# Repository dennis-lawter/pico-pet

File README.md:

# Pico Pet
A virtual pet that requires the user to complete pomodoros for the health of their pet.

## Hardware
- Raspberry Pi Pico
    - [Raspberry Pi Pico](https://www.raspberrypi.com/products/raspberry-pi-pico/) for development
    - [Waveshare RP2040-Tiny](https://www.waveshare.com/rp2040-tiny.htm) for release
- [Waveshare 1.44" LCD](https://www.waveshare.com/pico-lcd-1.44.htm)
- [DS3231](https://www.amazon.com/dp/B09KPC8JZQ/)
- Any 5v to 3v3 shifter for the DS3231, [for example](https://www.amazon.com/dp/B07LG646VS/)
- Any 5v speaker or buzzer, [for example](https://www.amazon.com/dp/B07P6X9YX7/)
- Any 3v-5v vibrating motor, [for example](https://www.amazon.com/dp/B073YFR5WR)

## NVM Utilization
The NVM (Non-Volatile Memory) module included with the DS3231 provides 4KiB arranged in 512 pages of 8 bytes each.

Permanent storage must be serializable to a specified number of pages, and write to an assigned page address.

Pages are addressed from hexidecimal 0x000 to 0x1ff.

| Page Start | Page End | Module |
| --- | --- | --- |
| 000 | 000 | Header |
| 001 | 002 | Settings |
| 003 | 003 | Inventory |
| 004 | 005 | Pet |

*note: If the NVM becomes corrupted, try changing the const `NVM_SENTINEL` to force a header guard check failure. This will factory reset the device, and all data will be lost.*
|  | **Header** |
| --- | --- |
| 0 | if set to the `NVM_SENTINEL` value, then the EEPROM is assumed to contain a valid savefile |
| 1 |  |
| 2 |  |
| 3 |  |
| 4 |  |
| 5 |  |
| 6 |  |
| 7 |  |

|  | **Settings Page 1** | min | max |
| --- | --- | --- | --- |
| 0 | User brightness | 0 | 15 |
| 1 | User volume | 0 | 4 |
| 2 | *nyi* Vibration enabled | 0 | 1 |
| 3 | *nyi* 12hr clock enabled | 0 | 1 |
| 4 | *nyi* minutes before device sleeps | 1 | 90 |
| 5 |  |  |  |
| 6 |  |  |  |
| 7 |  |  |  |

|  | **Settings Page 2** | min | max |
| --- | --- | --- | --- |
| 0 | Pomodoro length in minutes | 1 | 90 |
| 1 | Short break length in minutes | 1 | 90 |
| 2 | Long break length in minutes | 1 | 90 |
| 3 | Cycles, aka number of pomodoros before a long rest | 1 | 9 |
| 4 | Pet feeding deadline hr | 0 | 23 |
| 5 | Pet feeding deadline min | 0 | 59 |
| 6 |  |  |  |
| 7 |  |  |  |

|  | **Inventory** | min | max |
| --- | --- | --- | --- |
| 0 | Tomatoes | 0 | 99 |
| 1 | Raspberries | 0 | 9 |
| 2 | Lower byte of juice value |  |  |
| 3 | Higher byte of juice value |  |  |
| 4 |  |  |  |
| 5 |  |  |  |
| 6 |  |  |  |
| 7 |  |  |  |

Max juice is 9999ml as a u16

|  | **Pet Page 1** |
| --- | --- |
| 0 | Birth Day |
| 1 | Birth Month |
| 2 | Birth Year |
| 3 |  |
| 4 |  |
| 5 |  |
| 6 |  |
| 7 |  |

|  | **Pet Page 2** |
| --- | --- |
| 0 | Current HP |
| 1 | Sickness |
| 2 | Daily Hunger |
| 3 | Last Fed Day |
| 4 | Last Fed Month |
| 5 | Last Fed Year |
| 6 |  |
| 7 |  |

Max HP = Daily Hunger + 4

Last Fed Year is probably excessive,
but it'd be a weird bug if someone started the pet up after exactly 1 year,
and their pet showed no signs of missed days of hunger...

## Pin Out For Raspberry Pico

```mermaid
graph LR
    subgraph RP2040
        Pin1
        Pin2
        %%Pin3[GND]
        Pin4
        Pin5
        Pin6
        Pin7
        %%Pin8[GND]
        Pin9
        %%Pin10
        Pin11
        Pin12
        %%Pin13[GND]
        Pin14
        Pin15
        Pin16
        Pin17
        %%Pin18[GND]
        %%Pin19
        Pin20
        %%Pin21
        Pin22
        %%Pin23[GND]
        %%Pin24
        %%Pin25
        %%Pin26
        %%Pin27
        %%Pin28[GND]
        %%Pin29
        %%Pin30
        %%Pin31
        %%Pin32
        %%Pin33[GND]
        %%Pin34
        %%Pin35
        %%Pin36[3V3_OUT]
        %%Pin37[3V3_EN]
        %%Pin38[GND]
        %%Pin39[VSYS]
        %%Pin40[VBUS]
    end

    subgraph RTC_NVM
        RTC_SDA
        RTC_SCL
        RTC_SQW
    end
    Pin1[Pin1 I2C0_SDA] --> RTC_SDA
    Pin2[Pin2 I2C0_SCL] --> RTC_SCL
    Pin7[Pin7 GP5] --> RTC_SQW

    subgraph BUZZER
        SPEAKER
    end
    Pin6[Pin6 PWM_A2] --> SPEAKER

    subgraph VIBRATION
        MOTOR
    end
    Pin9[Pin9 GP6] --> MOTOR

    subgraph LCD
        LCD_KEY2
        LCD_KEY3
        LCD_DC
        LCD_CS
        LCD_CLK
        LCD_DIN
        LCD_RST
        LCD_BL
        LCD_KEY0
        LCD_KEY1
    end
    Pin4[Pin4 GP2] --> LCD_KEY2
    Pin5[Pin5 GP3] --> LCD_KEY3
    Pin11[Pin11 GP8] --> LCD_DC
    Pin12[Pin12 SPI1_CSn] --> LCD_CS
    Pin14[Pin14 SPI1_SCK] --> LCD_CLK
    Pin15[Pin15 SPI1_TX] --> LCD_DIN
    Pin16[Pin16 SPI1_RX] --> LCD_RST
    Pin17[Pin17 PWM_B6] --> LCD_BL
    Pin20[Pin20 GP15] --> LCD_KEY0
    Pin22[Pin22 GP17] --> LCD_KEY1
```

## Pinout for Waveshare RP2040-Tiny
```mermaid
graph LR
    subgraph RP2040-Tiny
        TinyPin0
        TinyPin1
        TinyPin2
        TinyPin3
        TinyPin4
        TinyPin5
        TinyPin6
        %%TinyPin7
        TinyPin8
        TinyPin9
        TinyPin10
        TinyPin11
        TinyPin12
        TinyPin13
        %%TinyPin14
        TinyPin15
        %%TinyPin16
        %%TinyPin17
        %%TinyPin18
        TinyPin19
        %%TinyPin20
        %%TinyPin21[3V3]
        %%TinyPin22[GND]
        %%TinyPin23[5V]
    end

    subgraph RTC_NVM
        RTC_SDA
        RTC_SCL
        RTC_SQW
    end
    TinyPin0[TinyPin0 I2C0_SDA] --> RTC_SDA
    TinyPin1[TinyPin1 I2C0_SCL] --> RTC_SCL
    TinyPin5[TinyPin5 GP5] --> RTC_SQW

    subgraph BUZZER
        SPEAKER
    end
    TinyPin4[TinyPin4 PWM_A2] --> SPEAKER

    subgraph VIBRATION
        MOTOR
    end
    TinyPin6[TinyPin6 GP6] --> MOTOR

    subgraph LCD
        LCD_KEY2
        LCD_KEY3
        LCD_DC
        LCD_CS
        LCD_CLK
        LCD_DIN
        LCD_RST
        LCD_BL
        LCD_KEY0
        LCD_KEY1
    end
    TinyPin2[TinyPin2 GP2] --> LCD_KEY2
    TinyPin3[TinyPin3 GP3] --> LCD_KEY3
    TinyPin8[TinyPin8 GP8] --> LCD_DC
    TinyPin9[TinyPin9 SPI1_CSn] --> LCD_CS
    TinyPin10[TinyPin10 SPI1_SCK] --> LCD_CLK
    TinyPin11[TinyPin11 SPI1_TX] --> LCD_DIN
    TinyPin12[TinyPin12 SPI1_RX] --> LCD_RST
    TinyPin13[TinyPin13 PWM_B6] --> LCD_BL
    TinyPin15[TinyPin15 GP15] --> LCD_KEY0
    TinyPin19[TinyPin19 GP29] --> LCD_KEY1
```

## Development Breakboard Build
Below are my recommendations for how to build the development board.

### Shopping List
All amazon links are tracking free and affiliate free; feel free to source these where you wish, but compatability is not guaranteed for other similar products.
The current iteration of the software is absolutely tied to the LCD module below, as well as the combination DS3231 & AT24C32 board.
Theoretically any RTC and NVM module could replace the aformentioned, but the I2C addresses have been set to match the product below.
Additionally, any ST7735S driven 128x128 display could be adapted. All four buttons provided on the waveshare LCD hat are used as well.
- Components
    - Expansion Board https://www.amazon.com/dp/B08X6FPRYF/
    - Breakout Board https://www.amazon.com/dp/B0B982B9HV/
    - Breadboard https://www.amazon.com/dp/B07VFFXPH3/
    - LCD Module https://www.amazon.com/dp/B0957NJP97/
    - Raspberry Pico w/ presoldered headers https://www.amazon.com/dp/B08X7HN2VG/
    - RTC Board https://www.amazon.com/dp/B09KPC8JZQ/
    - Vibrating Motor https://www.amazon.com/dp/B073YFR5WR/
    - Piezo Buzzer https://www.amazon.com/dp/B07P6X9YX7/
- Tools/Resources
    - 22 AWG solid hookup wire https://www.amazon.com/dp/B07TX6BX47/
    - 22 AWG wire stripper https://www.amazon.com/dp/B06X9875Z7/
    - CR2032 battery https://www.amazon.com/dp/B071D4DKTZ/
    - Command strip https://www.amazon.com/dp/B07P32RHQ4/

### Assembly
1. Socket the Raspberry Pico into center of the Expansion Board.
2. Socket the LCD Module into the left slot of the Expansion Board.
3. Using a command strip, attach the breadboard to the flat side of the breakout board.
    - The 1A point of the breadboard should be in the top left, near where the word VBUS is printed on the back of the breakout board.
    - While many breadboards do come with stickers, there is often no solid insulating layer for the conductive rails, and the breakout board has sharp solder points that can stab through this thin soft layer. Whatever you do, I recommend insulating these two boards or you will risk a short...
4. Connect the breakout terminal VSYS and tie point 1A on the breadboard, preferably using a red wire.
    - I recommend running this wire over the top of the board rather than the side as it would be natural to do, because there will be essentially no space between the Raspberry Pico and this specific Breakout Board when they are eventually mated.
5. Connect the breakout terminal GND (the one adjacent to VSYS) and tie point 2A on the breadboard, preferably using a black wire.
    - Again, I recommend running this wire over the top of the board.
6. Connect the data lines to the breadboard, this time allowing the wires to wrap around the side of the board (recommended colors in parenthesis):
    - GP0 to J1 (green)
    - GP1 to J2 (white)
    - GP4 to J5 (yellow)
    - GP5 to J6 (blue)
    - GP6 to J7 (green)
7. Connect new lines on the breadboard for the RTC module:
    - C2 to C3 (black)
    - D1 to D4 (red)
    - H1 to B5 (green)
    - H2 to B6 (white)
    - H6 to B7 (blue) (I recommend routing this cable up then following the other 2 data lines)
8. Connect new lines on the breadboard for the piezo buzzer:
    - G5 to F17 (orange)
    - E2 to G13 (black) (I recommend routing this along the top side, then down the gap I left in the I column)
9. Connect new lines on the breadboard for the vibration motor:
    - G7 to K16 (green)
    - F13 to F15 (black)
10. Stick the vibration motor onto the bottom of the breadboard.
11. Attach the vibration motor wires (letting the wires lay to the right):
    - red wire to G16
    - blue wire to G15
12. Place the piezo buzzer onto pins J17 and J13 (placement will secure the vibration motor wires)
13. Insert a CR2032 battery into the RTC module.
14. Place the RTC module onto pins A3, A4, A5, A6, A7, and A8.
15. Finally, socket the breakout board onto the right slot of the Expansion Board.

### Development Environment Setup
#### NixOS
I recommend running the following to open the VSCodium development environment:
```bash
nix develop --command codium .
```

You can of course just use whatever text editor you like, and simply enter the flake in a terminal with:
```bash
nix develop
```

#### Arch
```
sudo pacman -S rustup
rustup default nightly
cargo install elf2uf2-rs
```
When the pico is plugged in you'll be prompted to mount the device. You must mount and run the device for this process to complete successfully.

#### Other Linux Distros
You'll need Rust installed and set to nightly-2023-11-16. Other versions may not be supported. You will likely also need udev to detect the raspberry pico. To use the makefile, you'll also want gnu make. You can review the `flake.nix` and attempt to reproduce it in your own OS.

### First Time Setup
Your first time opening this repo, you'll need to setup the dependencies and enable the thumbv6m-none-eabi target. This has been automated for you:
```bash
make init
```

### Running The Code
The build process performs a number of actions. The sprites will be converted from PNG files to raw binary files containing RGB332 data. Fonts will be converted from PNG files to binary files containg black&white data. The custom PEAT audio files will be converted from plaintext files to the binary custom BEAT format. With all assets converted, the project will finally build and attempt to upload.

All of this is as simple as invoking:
```bash
make run
```

## Attributions
Placeholder artwork (lofi.png) copyright belongs to Juan Pablo Machado.

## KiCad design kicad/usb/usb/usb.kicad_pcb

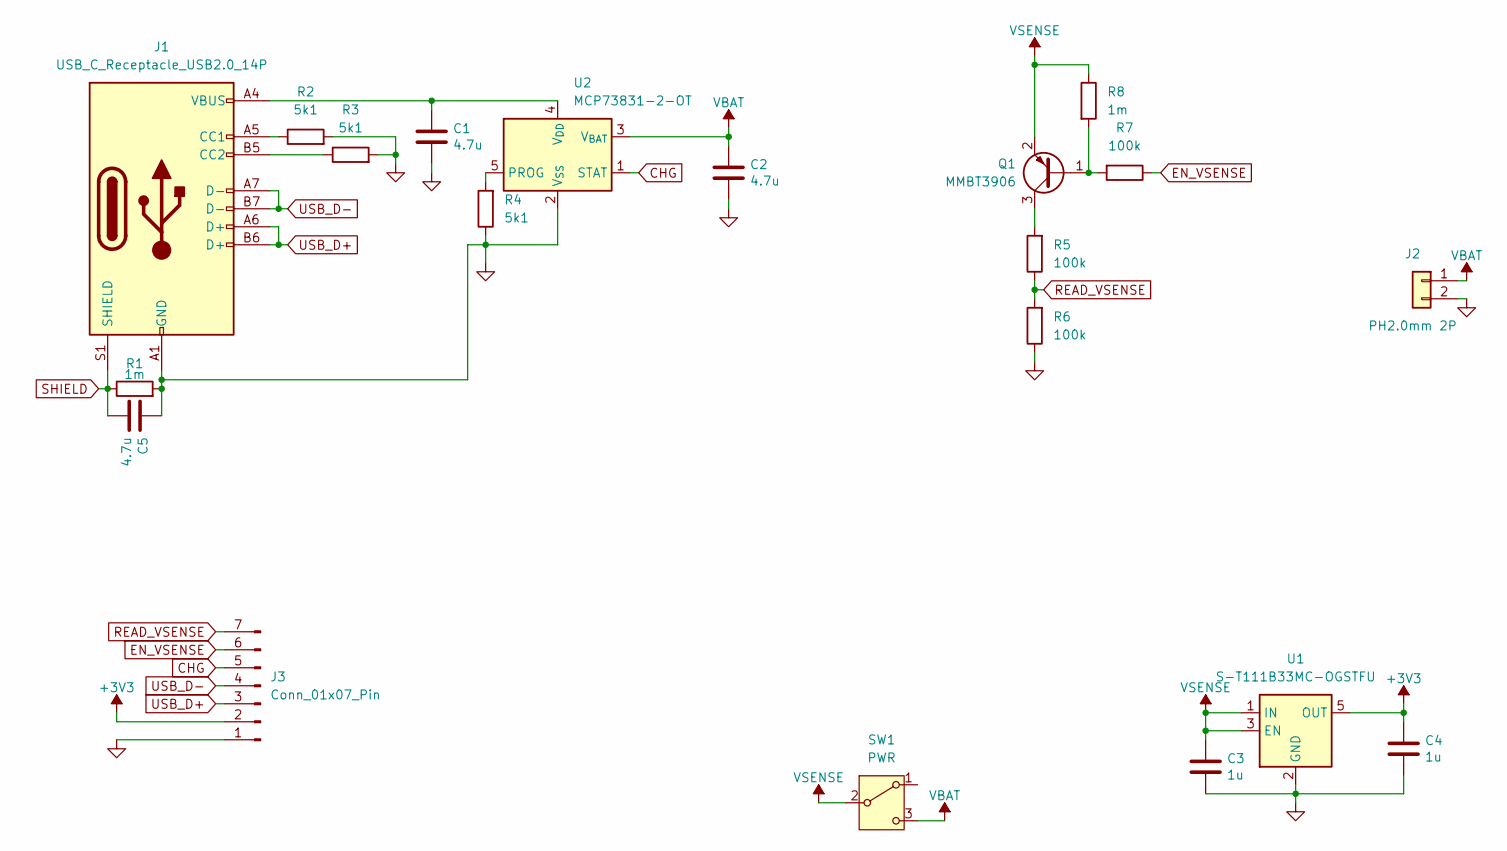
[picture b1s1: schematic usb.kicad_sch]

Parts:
C1, C2: 4.7u; C_0805_2012Metric; LCSC C15850
C3, C4: 1u; C_0805_2012Metric; LCSC C15850
C5: 4.7u; C_0603_1608Metric_Pad1.08x0.95mm_HandSolder; LCSC C15850
J1: USB_C_Receptacle_USB2.0_14P; USB_C_Receptacle_GCT_USB4105-xx-A_16P_TopMnt_Horizontal
J2: PH2.0mm 2P; JST_PH_S2B-PH-K_1x02_P2.00mm_Horizontal; LCSC C124375
J3: Conn_01x07_Pin; PinHeader_1x07_P2.54mm_Vertical
Q1: MMBT3906; SOT-23
R1: 1m; R_0603_1608Metric_Pad0.98x0.95mm_HandSolder
R2, R3, R4: 5k1; R_0201_0603Metric_Pad0.64x0.40mm_HandSolder
R5, R6, R7: 100k; R_0402_1005Metric_Pad0.72x0.64mm_HandSolder
R8: 1m; R_0402_1005Metric_Pad0.72x0.64mm_HandSolder
SW1: PWR; SW_Slide_SPDT_Angled_CK_OS102011MA1Q
U1: S-T111B33MC-OGSTFU; SOT-23-5
U2: MCP73831-2-OT; SOT-23-5

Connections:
+3V3: C4.1, J3.2, U1.5 (OUT)
CHG: J3.5, U2.1 (STAT)
EN_VSENSE: J3.6, R7.1
GND: C1.2, C2.2, C3.2, C4.2, C5.1, J1.A1 (GND), J1.A12 (GND), J1.B1 (GND), J1.B12 (GND), J2.2, J3.1, R1.2, R2.2, R3.2, R4.1, R6.1, U1.2 (GND), U1.4 (GND), U2.2 (V_{SS})
unnamed: J1.A5 (CC1), R2.1
unnamed: J1.B5 (CC2), R3.1
unnamed: Q1.1 (B), R7.2, R8.2
unnamed: Q1.3 (C), R5.2
unnamed: R4.2, U2.5 (PROG)
unnamed: C1.1, J1.A4 (VBUS), J1.A9 (VBUS), J1.B4 (VBUS), J1.B9 (VBUS), U2.4 (V_{DD})
READ_VSENSE: J3.7, R5.1, R6.2
SHIELD: C5.2, J1.S1 (SHIELD), R1.1
USB_D+: J1.A6 (D+), J1.B6 (D+), J3.3
USB_D-: J1.A7 (D-), J1.B7 (D-), J3.4
VBAT: C2.1, J2.1, SW1.3 (C), U2.3 (V_{BAT})
VSENSE: C3.1, Q1.2 (E), R8.1, SW1.2 (B), U1.1 (IN), U1.3 (EN)

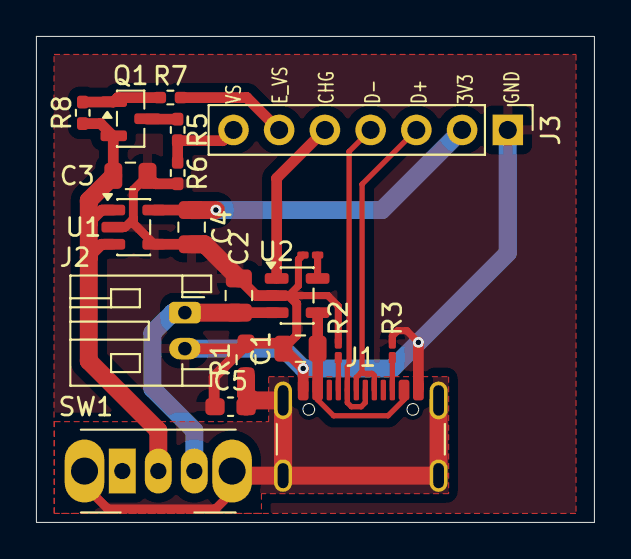
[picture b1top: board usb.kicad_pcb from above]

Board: 2 copper layers, 31.0 x 27.0 mm, 20 parts (0 on the bottom side), 16 nets.

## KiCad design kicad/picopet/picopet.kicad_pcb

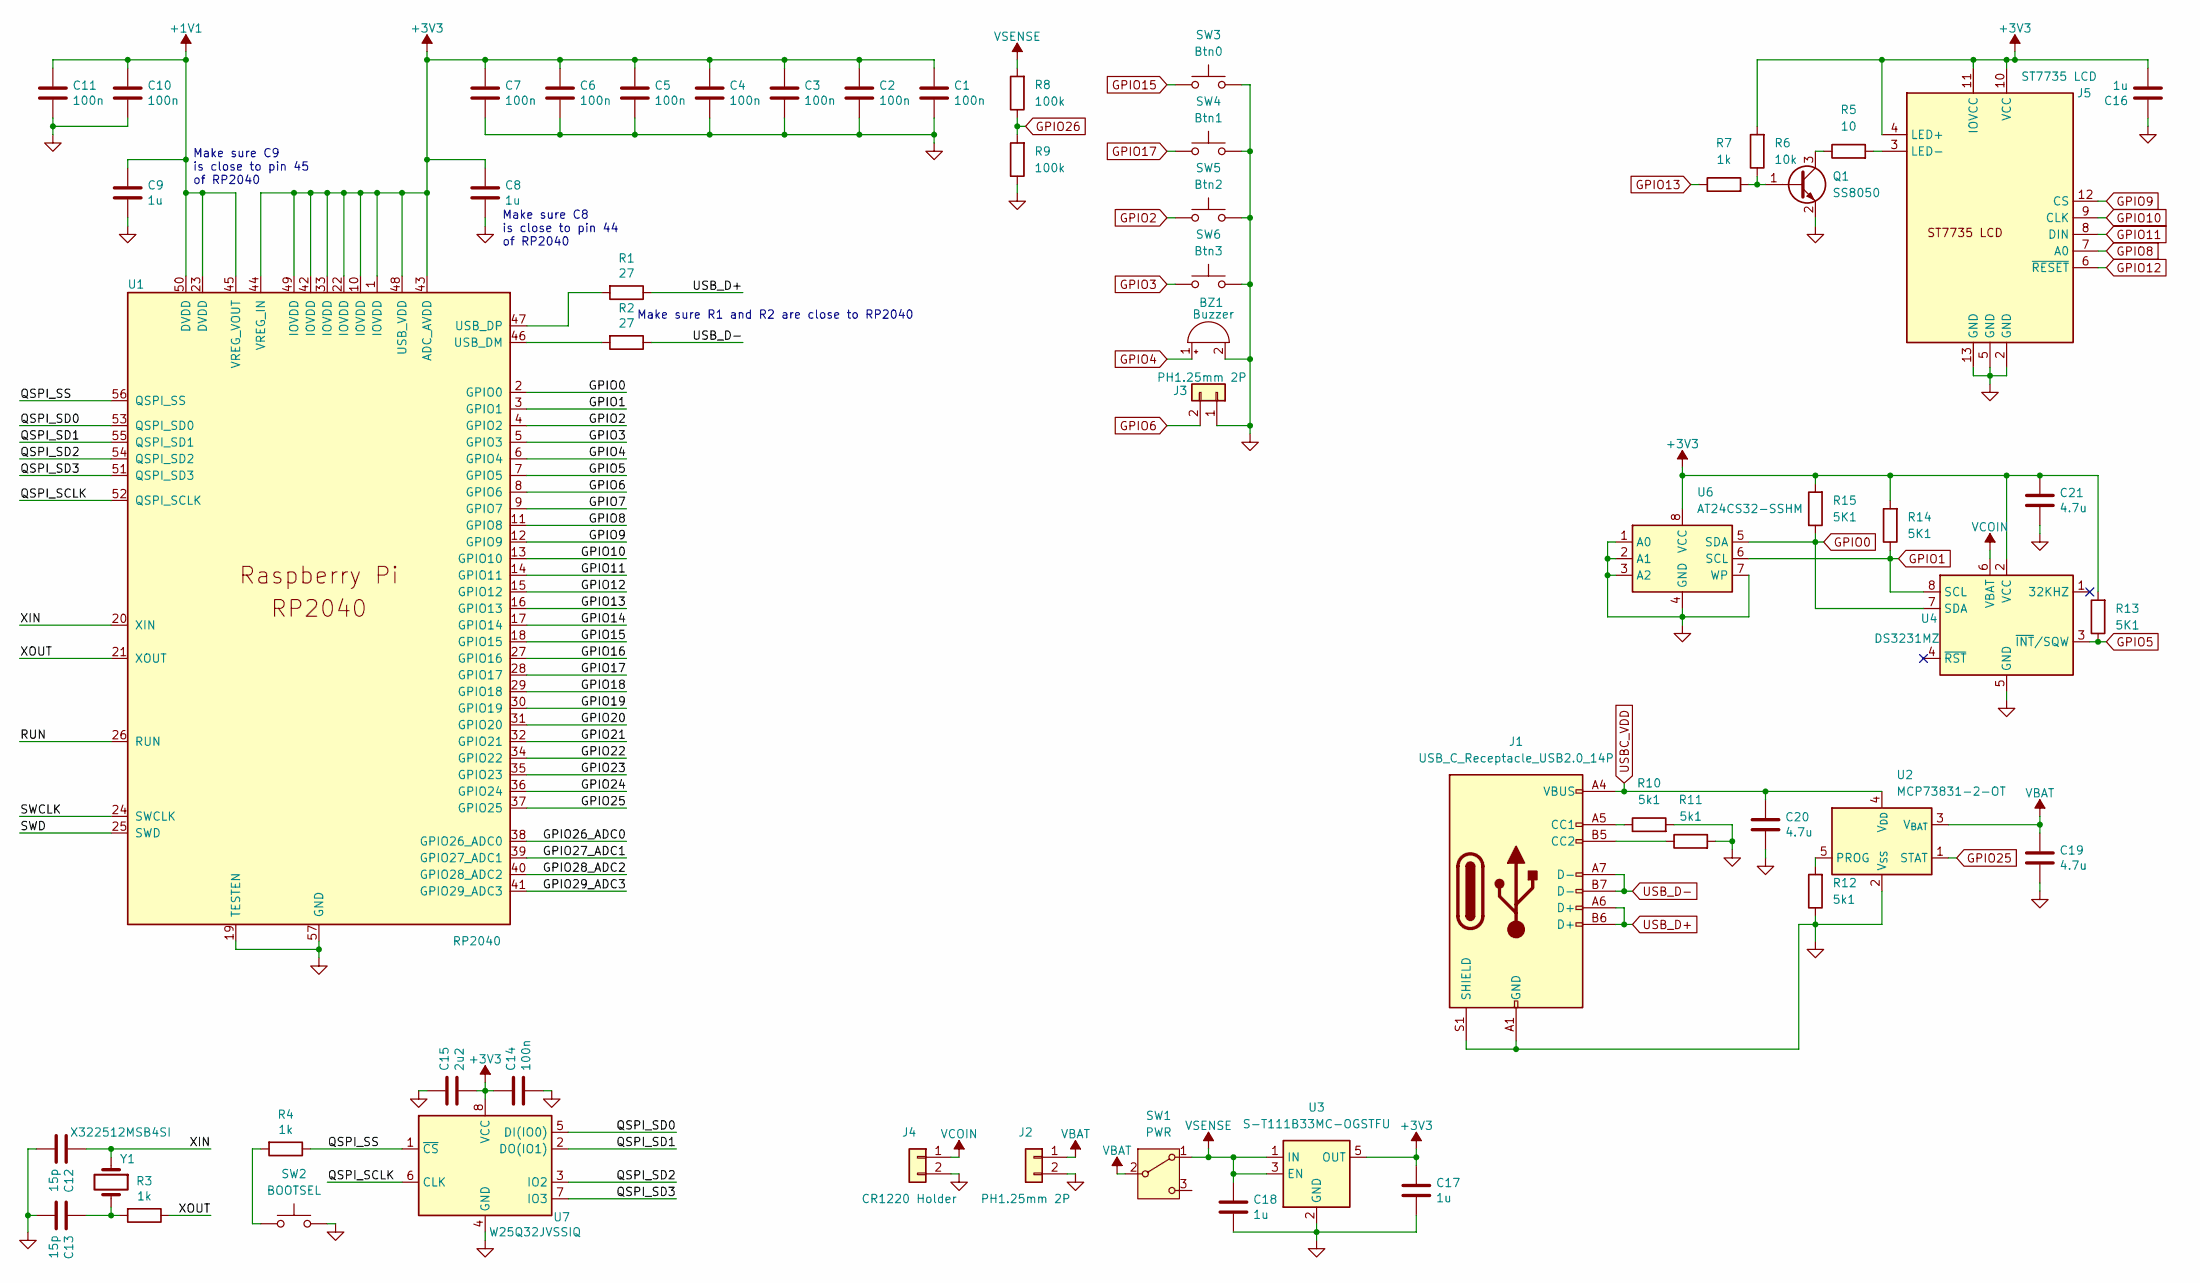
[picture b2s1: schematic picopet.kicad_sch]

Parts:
BZ1: Buzzer; MagneticBuzzer_CUI_CMT-8504-100-SMT
C1, C2, C3, C4, C5, C6, C7, C10, C11, C14: 100n; C_0402_1005Metric; LCSC C126504
C8, C9: 1u; C_0402_1005Metric; LCSC C307331
C12, C13: 15p; C_0402_1005Metric; LCSC C52923
C15: 2u2; C_0402_1005Metric; LCSC C126504
C16: 1u; C_0402_1005Metric; LCSC C126504
C17, C18: 1u; C_0805_2012Metric; LCSC C15850
C19, C20, C21: 4.7u; C_0805_2012Metric; LCSC C15850
J1: USB_C_Receptacle_USB2.0_14P; USB_C_Receptacle_GCT_USB4105-xx-A_16P_TopMnt_Horizontal
J2, J3: PH1.25mm 2P; JST_GH_SM02B-GHS-TB_1x02-1MP_P1.25mm_Horizontal; LCSC C124375
J4: CR1220 Holder; BatteryHolder_LINX_BAT-HLD-012-SMT; LCSC C124375
J5: ST7735 LCD; ST7735_P0.8mm
Q1: SS8050; SOT-23
R1, R2: 27; R_0201_0603Metric; LCSC C274349
R3: 1k; R_0402_1005Metric; LCSC C11702
R4: 1k; R_0201_0603Metric; LCSC C11702
R5: 10; R_0201_0603Metric
R6: 10k; R_0201_0603Metric
R7: 1k; R_0201_0603Metric
R8, R9: 100k; R_0402_1005Metric
R10, R11, R12: 5k1; R_0201_0603Metric
R13, R14, R15: 5K1; R_0201_0603Metric
SW1: PWR; SW_SPDT_CK_JS102011SAQN
SW2: BOOTSEL; SW_SPST_EVQP2_MiddlePushTravel_H2.5mm
SW3: Btn0; SW_SPST_EVQP2_MiddlePushTravel_H2.5mm
SW4: Btn1; SW_SPST_EVQP2_MiddlePushTravel_H2.5mm
SW5: Btn2; SW_SPST_EVQP2_MiddlePushTravel_H2.5mm
SW6: Btn3; SW_SPST_EVQP2_MiddlePushTravel_H2.5mm
U1: RP2040; QFN-56-1EP_7x7mm_P0.4mm_EP3.2x3.2mm; LCSC C2040
U2: MCP73831-2-OT; SOT-23-5
U3: S-T111B33MC-OGSTFU; SOT-23-5
U4: DS3231MZ; SOIC-8_3.9x4.9mm_P1.27mm
U6: AT24CS32-SSHM; SOIC-8_3.9x4.9mm_P1.27mm
U7: W25Q32JVSSIQ; SOIC-8_3.9x4.9mm_P1.27mm; LCSC C97521
Y1: X322512MSB4SI; Crystal_SMD_3225-4Pin_3.2x2.5mm; LCSC C110563

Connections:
+1V1: C9.1, C10.1, C11.1, U1.23 (DVDD), U1.45 (VREG_VOUT), U1.50 (DVDD)
+3V3: C1.1, C2.1, C3.1, C4.1, C5.1, C6.1, C7.1, C8.1, C14.1, C15.2, C16.2, C17.1, C21.1, J5.4 (LED+), J5.10 (VCC), J5.11 (IOVCC), R6.2, R13.2, R14.2, R15.2, U1.1 (IOVDD), U1.10 (IOVDD), U1.22 (IOVDD), U1.33 (IOVDD), U1.42 (IOVDD), U1.43 (ADC_AVDD), U1.44 (VREG_IN), U1.48 (USB_VDD), U1.49 (IOVDD), U3.5 (OUT), U4.2 (VCC), U6.8 (VCC), U7.8 (VCC)
/GPIO7: U1.9 (GPIO7)
/GPIO14: U1.17 (GPIO14)
/GPIO16: U1.27 (GPIO16)
/GPIO18: U1.29 (GPIO18)
/GPIO19: U1.30 (GPIO19)
/GPIO20: U1.31 (GPIO20)
/GPIO21: U1.32 (GPIO21)
/GPIO22: U1.34 (GPIO22)
/GPIO23: U1.35 (GPIO23)
/GPIO24: U1.36 (GPIO24)
/GPIO26_ADC0: U1.38 (GPIO26_ADC0)
/GPIO27_ADC1: U1.39 (GPIO27_ADC1)
/GPIO28_ADC2: U1.40 (GPIO28_ADC2)
/GPIO29_ADC3: U1.41 (GPIO29_ADC3)
/QSPI_SCLK: U1.52 (QSPI_SCLK), U7.6 (CLK)
/QSPI_SD0: U1.53 (QSPI_SD0), U7.5 (DI(IO0))
/QSPI_SD1: U1.55 (QSPI_SD1), U7.2 (DO(IO1))
/QSPI_SD2: U1.54 (QSPI_SD2), U7.3 (IO2)
/QSPI_SD3: U1.51 (QSPI_SD3), U7.7 (IO3)
/QSPI_SS: R4.1, U1.56 (QSPI_SS), U7.1 (~CS)
/RUN: U1.26 (RUN)
/SWCLK: U1.24 (SWCLK)
/SWD: U1.25 (SWD)
/XIN: C12.1, U1.20 (XIN), Y1.1
/XOUT: R3.1, U1.21 (XOUT)
GND: BZ1.2 (-), C1.2, C2.2, C3.2, C4.2, C5.2, C6.2, C7.2, C8.2, C9.2, C10.2, C11.2, C12.2, C13.2, C14.2, C15.1, C16.1, C17.2, C18.2, C19.2, C20.2, C21.2, J1.A1 (GND), J1.A12 (GND), J1.B1 (GND), J1.B12 (GND), J1.S1 (SHIELD), J2.2, J3.1, J4.2, J5.2 (GND), J5.5 (GND), J5.13 (GND), Q1.2 (E), R9.1, R10.2, R11.2, R12.1, SW2.2, SW3.2, SW4.2, SW5.2, SW6.2, U1.19 (TESTEN), U1.57 (GND), U2.2 (V_{SS}), U3.2 (GND), U3.4 (GND), U4.5 (GND), U6.1 (A0), U6.2 (A1), U6.3 (A2), U6.4 (GND), U6.7 (WP), U7.4 (GND)
GPIO0: R15.1, U1.2 (GPIO0), U4.7 (SDA), U6.5 (SDA)
GPIO1: R14.1, U1.3 (GPIO1), U4.8 (SCL), U6.6 (SCL)
GPIO2: SW5.1, U1.4 (GPIO2)
GPIO3: SW6.1, U1.5 (GPIO3)
GPIO4: BZ1.1 (+), U1.6 (GPIO4)
GPIO5: R13.1, U1.7 (GPIO5), U4.3 (~INT/SQW)
GPIO6: J3.2, U1.8 (GPIO6)
GPIO8: J5.7 (A0), U1.11 (GPIO8)
GPIO9: J5.12 (CS), U1.12 (GPIO9)
GPIO10: J5.9 (CLK), U1.13 (GPIO10)
GPIO11: J5.8 (DIN), U1.14 (GPIO11)
GPIO12: J5.6 (~RESET), U1.15 (GPIO12)
GPIO13: R7.1, U1.16 (GPIO13)
GPIO15: SW3.1, U1.18 (GPIO15)
GPIO17: SW4.1, U1.28 (GPIO17)
GPIO25: U1.37 (GPIO25), U2.1 (STAT)
GPIO26: R8.1, R9.2
unnamed: C13.1, R3.2, Y1.2
unnamed: J1.A5 (CC1), R10.1
unnamed: J1.B5 (CC2), R11.1
unnamed: J5.3 (LED-), R5.2
unnamed: Q1.1 (B), R6.1, R7.2
unnamed: Q1.3 (C), R5.1
unnamed: R4.2, SW2.1
unnamed: R2.2, U1.46 (USB_DM)
unnamed: R1.2, U1.47 (USB_DP)
unnamed: R12.2, U2.5 (PROG)
USBC_VDD: C20.1, J1.A4 (VBUS), J1.A9 (VBUS), J1.B4 (VBUS), J1.B9 (VBUS), U2.4 (V_{DD})
USB_D+: J1.A6 (D+), J1.B6 (D+), R1.1
USB_D-: J1.A7 (D-), J1.B7 (D-), R2.1
VBAT: C19.1, J2.1, SW1.2 (B), U2.3 (V_{BAT})
VCOIN: J4.1, U4.6 (VBAT)
VSENSE: C18.1, R8.2, SW1.1 (A), U3.1 (IN), U3.3 (EN)

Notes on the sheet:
Make sure R1 and R2 are close to RP2040
Make sure C9 is close to pin 45 of RP2040
Make sure C8 is close to pin 44 of RP2040

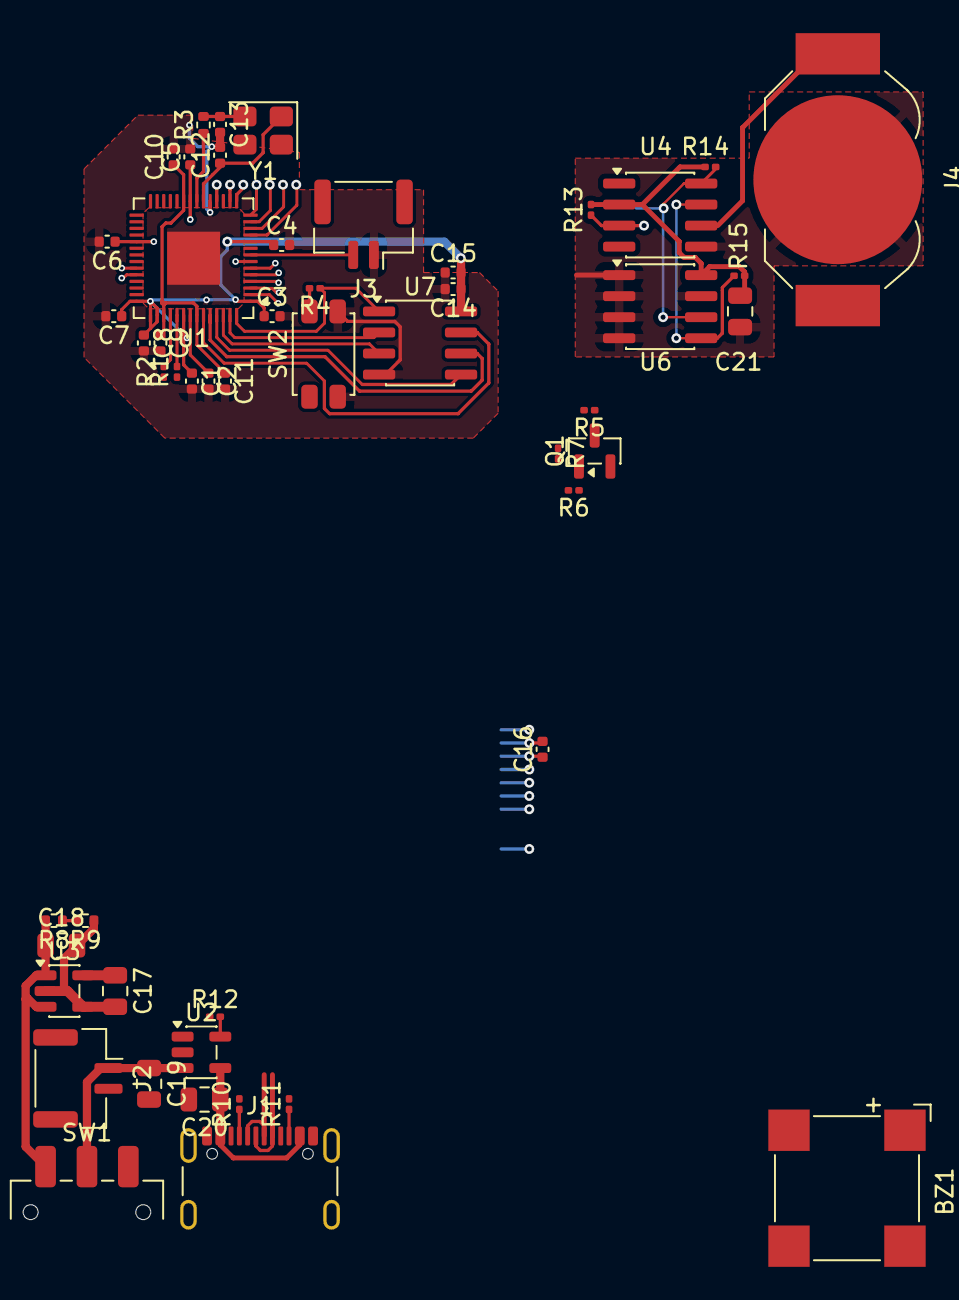
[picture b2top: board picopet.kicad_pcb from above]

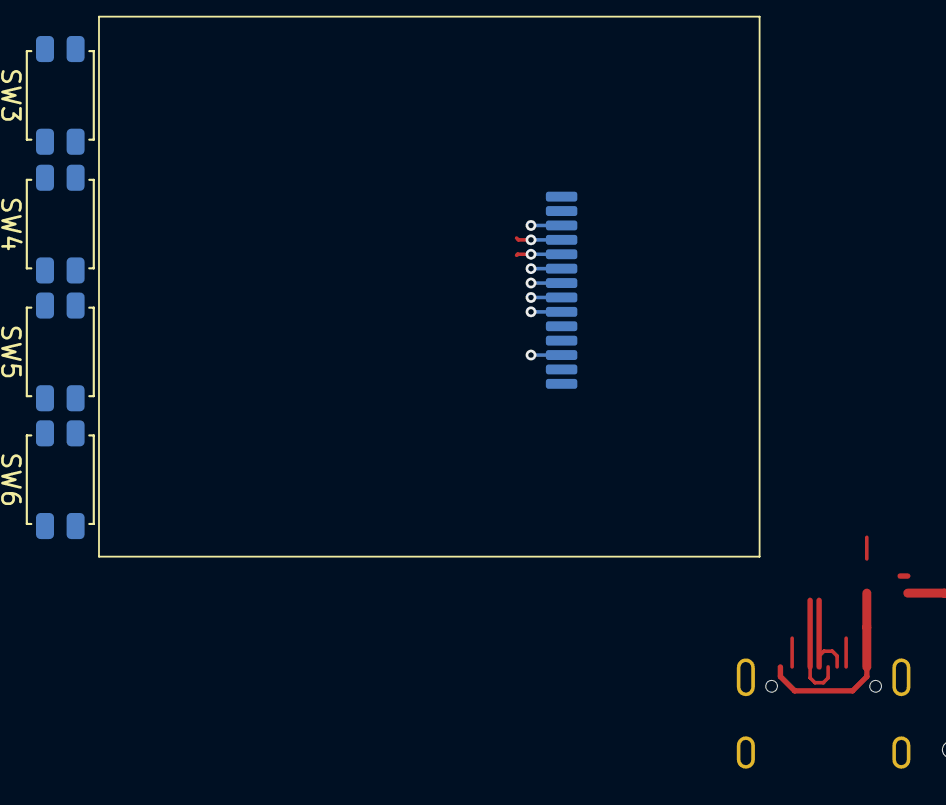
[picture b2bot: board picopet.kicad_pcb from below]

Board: 2 copper layers, 56 parts (5 on the bottom side), 44 nets.

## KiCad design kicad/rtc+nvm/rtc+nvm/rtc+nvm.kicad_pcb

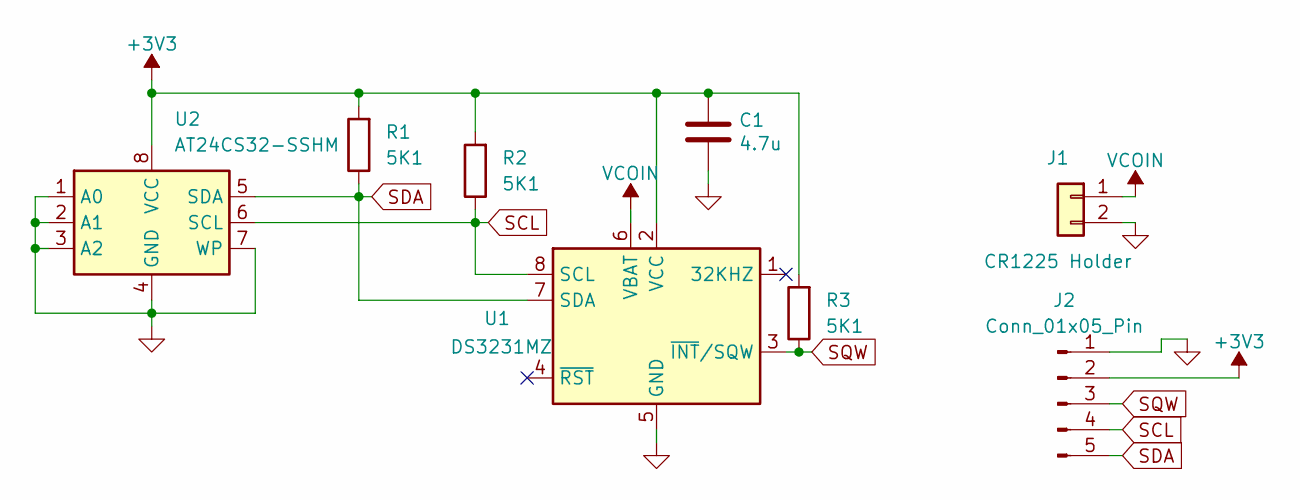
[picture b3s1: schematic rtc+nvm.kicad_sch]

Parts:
C1: 4.7u; C_0805_2012Metric; LCSC C15850
J1: CR1225 Holder; BatteryHolder_LINX_BAT-HLD-012-SMT; LCSC C124375
J2: Conn_01x05_Pin; PinHeader_1x05_P2.54mm_Vertical
R1, R2, R3: 5K1; R_0402_1005Metric_Pad0.72x0.64mm_HandSolder
U1: DS3231MZ; SOIC-8_3.9x4.9mm_P1.27mm
U2: AT24CS32-SSHM; SOIC-8_3.9x4.9mm_P1.27mm

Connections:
+3V3: C1.1, J2.2, R1.2, R2.2, R3.2, U1.2 (VCC), U2.8 (VCC)
GND: C1.2, J1.2, J2.1, U1.5 (GND), U2.1 (A0), U2.2 (A1), U2.3 (A2), U2.4 (GND), U2.7 (WP)
SCL: J2.4, R2.1, U1.8 (SCL), U2.6 (SCL)
SDA: J2.5, R1.1, U1.7 (SDA), U2.5 (SDA)
SQW: J2.3, R3.1, U1.3 (~INT/SQW)
VCOIN: J1.1, U1.6 (VBAT)

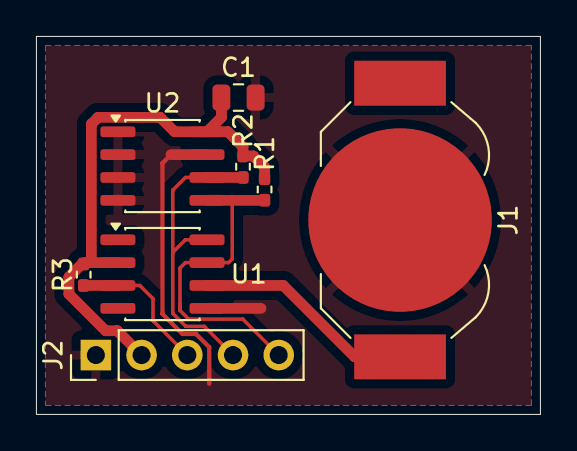
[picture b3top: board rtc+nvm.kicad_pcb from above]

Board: 2 copper layers, 28.0 x 21.0 mm, 8 parts (0 on the bottom side), 6 nets.

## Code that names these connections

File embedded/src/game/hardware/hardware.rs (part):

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
type DisplaySdi = rp2040_hal::Spi<rp2040_hal::spi::Enabled, pac::SPI1, 8>;
type DisplayDc = rp2040_hal::gpio::Pin<
    rp2040_hal::gpio::bank0::Gpio8,
    rp2040_hal::gpio::Output<rp2040_hal::gpio::PushPull>,
>;
type DisplayRst = rp2040_hal::gpio::Pin<
    rp2040_hal::gpio::bank0::Gpio12,
    rp2040_hal::gpio::Output<rp2040_hal::gpio::PushPull>,
>;

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type BuzzerPwmSlice = rp2040_hal::pwm::Slice<rp2040_hal::pwm::Pwm2, rp2040_hal::pwm::FreeRunning>;

type Key0Pin = rp2040_hal::gpio::Pin<
    rp2040_hal::gpio::bank0::Gpio15,
    rp2040_hal::gpio::Input<rp2040_hal::gpio::PullUp>,
>;
type Key1Pin = rp2040_hal::gpio::Pin<
    rp2040_hal::gpio::bank0::Gpio17,
    rp2040_hal::gpio::Input<rp2040_hal::gpio::PullUp>,
>;
type Key2Pin = rp2040_hal::gpio::Pin<
    rp2040_hal::gpio::bank0::Gpio2,
    rp2040_hal::gpio::Input<rp2040_hal::gpio::PullUp>,
>;
type Key3Pin = rp2040_hal::gpio::Pin<
    rp2040_hal::gpio::bank0::Gpio3,
    rp2040_hal::gpio::Input<rp2040_hal::gpio::PullUp>,
>;
type Key5Pin = rp2040_hal::gpio::Pin<
    rp2040_hal::gpio::bank0::Gpio5,
    rp2040_hal::gpio::Input<rp2040_hal::gpio::PullUp>,
>;

type Adc0Pin = rp2040_hal::gpio::Pin<
    rp2040_hal::gpio::bank0::Gpio26,
    rp2040_hal::gpio::Input<rp2040_hal::gpio::Floating>,
>;

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// >;

type VibePin = rp2040_hal::gpio::Pin<
    rp2040_hal::gpio::bank0::Gpio6,
    rp2040_hal::gpio::Output<rp2040_hal::gpio::PushPull>,
>;

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    pac::I2C0,
    (
        rp2040_hal::gpio::Pin<
            rp2040_hal::gpio::bank0::Gpio0,
            rp2040_hal::gpio::Function<rp2040_hal::gpio::I2C>,
        >,
        rp2040_hal::gpio::Pin<
            rp2040_hal::gpio::bank0::Gpio1,
            rp2040_hal::gpio::Function<rp2040_hal::gpio::I2C>,
        >,
    ),
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    pub fifo_ptr: *mut SioFifo,
    pub i2c_bus: I2CBus,
    pub adc: Adc,
    pub vsense_pin: Adc0Pin,
    // pub vsense_enable_pin: VsenseEnablePin,
    pub nvm_addr: u8,
}
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            // Output channel B on PWM6 to GPIO 13
            let backlight_channel_ptr = &mut pwm6.channel_b as *mut LcdBlPinChannel;
            // disable backlight ASAP to hide boot artifacts
            (*backlight_channel_ptr).output_to(pins.gpio13);
            (*backlight_channel_ptr).enable();
            (*backlight_channel_ptr).set_duty(0);

            let buzzer_channel_ptr =
                &mut (*buzzer_pwm_slice_ptr).channel_a as *mut BuzzerPinChannel;
            (*buzzer_channel_ptr).output_to(pins.gpio4);
            (*buzzer_channel_ptr).enable();
            (*buzzer_channel_ptr).set_duty(0);

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            (*buzzer_pwm_slice_ptr).set_top(0);
            (*buzzer_pwm_slice_ptr).enable();

            let key0 = pins.gpio15.into_pull_up_input();
            let key1 = pins.gpio17.into_pull_up_input();
            let key2 = pins.gpio2.into_pull_up_input();
            let key3 = pins.gpio3.into_pull_up_input();

            let second_clock = pins.gpio5.into_pull_up_input();

            let mut vsense_enable_pin = pins.gpio22.into_push_pull_output();
            vsense_enable_pin.set_high().unwrap();

            let adc: Adc = Adc::new(pac.ADC, &mut pac.RESETS);
            let vsense_pin = pins.gpio26.into_floating_input();

            let mut vibe = pins.gpio6.into_push_pull_output();
            vibe.set_low().unwrap();

            let sys_freq = clocks.system_clock.freq().to_Hz();
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
            let (mut _pio, _sm0, _, _, _) = pac.PIO0.split(&mut pac.RESETS);

            let lcd_dc = pins.gpio8.into_push_pull_output();
            let mut _lcd_cs = pins.gpio9.into_mode::<rp2040_hal::gpio::FunctionSpi>();
            let mut _lcd_clk = pins.gpio10.into_mode::<rp2040_hal::gpio::FunctionSpi>();
            let mut _lcd_mosi = pins.gpio11.into_mode::<rp2040_hal::gpio::FunctionSpi>();
            let lcd_rst = pins
                .gpio12
                .into_push_pull_output_in_state(rp2040_hal::gpio::PinState::High);

            let spi = rp2040_hal::Spi::<_, _, 8>::new(pac.SPI1);
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                .clear(Rgb565::BLACK)
                .expect("Could not initialize display");

            let sda_pin = pins.gpio0.into_mode::<rp2040_hal::gpio::FunctionI2C>();
            let scl_pin = pins.gpio1.into_mode::<rp2040_hal::gpio::FunctionI2C>();

            let mut i2c_bus: I2CBus = rp2040_hal::I2C::i2c0(
                pac.I2C0,
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                fifo_ptr,
                i2c_bus,
                adc,
                vsense_pin,
                // vsense_enable_pin,
                nvm_addr,
            };
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            Adc,
            u16,
            rp2040_hal::gpio::Pin<
                rp2040_hal::gpio::bank0::Gpio26,
                rp2040_hal::gpio::Input<rp2040_hal::gpio::Floating>,
            >,
        >>::read(&mut self.adc, &mut self.vsense_pin);
        // self.vsense_enable_pin.set_low().unwrap();
        match r {
            Ok(val) => val,
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
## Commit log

2023-08-15 First commit, backlight flickers
2023-08-15 No progress yet
2023-08-15 IT WORKS
2023-08-16 Cutting down some chaff
2023-08-16 Rebrand and cleanup
2023-08-16 Removed warning
2023-08-16 Cleaned up main
2023-08-16 User input demo
2023-08-17 Clocked single core at 12fps with minor calcs
2023-08-17 Unsafe rust is terrifying
2023-08-17 Second core is activated...
2023-08-17 Cleanup
2023-08-17 Huge progress for RGB332 and differential drawing
2023-08-17 Missed changes
2023-08-21 Edge detection no good but somewhat working
2023-08-21 blit off edge working
2023-08-21 Optimization and second Ferris
2023-08-21 Added a flood fill
2023-08-21 Rudimentary glyph testing
2023-08-21 Text blitting
2023-08-21 str blit
2023-08-21 Fancy dialog box
2023-08-22 Create LICENSE
2023-08-22 Need font selection, but 5x8 works
2023-08-22 Basic font selection
2023-08-22 demo for fs_dialog (press key0+key3)
2023-08-23 Color interpolation in strings
2023-08-23 Error handling
2023-08-24 No input, but cpu1 handles graphics
2023-08-24 Delegated rendering to sprites
2023-08-24 Generalized text drawing
2023-08-24 Removed unused file
2023-08-24 Partial spritesheet solution
2023-08-25 Brightness setting
2023-08-25 Pointer cleanup
2023-08-25 Smalelr brightness range
2023-08-25 Refactored settings to struct
2023-08-25 Prototype of icon font
2023-08-26 Findings mostly in comments
2023-08-26 Piezo buzzer
2023-08-26 Ascending notes demo
2023-08-27 Compiles but does not run
2023-08-27 main cleanup
2023-08-27 Project files reorganized
2023-08-27 Simple state machine
2023-08-29 Music example, alternate pin for key1
2023-08-29 Greatly improved menu
2023-08-30 Update sprite factory constructors
2023-08-30 Slight volume adjustment
2023-08-30 Allowed variable ranges for settings
2023-08-31 Menu causing issues
2023-09-01 Menu functioning
2023-09-01 Stricter enum for menus
2023-09-01 Reorganization
2023-09-01 enum refactored
2023-09-02 Menu beeps
2023-09-02 Placeholder food symbol
2023-09-02 Labeled feed menu option
2023-09-02 not yet implemented feeding state
2023-09-03 State placeholders
2023-09-03 match cleanup
2023-09-06 cool panic handler, no progress on rtc
2023-09-06 stripped down code
2023-09-06 Stripped down project to bare main.rs
2023-09-12 Got a successful read
2023-09-12 Moved audio pin
2023-09-12 On-screen clock in settings menu
2023-09-12 Adjust time setting works
2023-09-12 Renamed system to hardware
2023-09-12 Moving hardware to global...
2023-09-12 Global hardware fully utilized
2023-09-12 Major state manager refactor
2023-09-12 RP2040-Tiny pinout
2023-09-13 Structure refactored
2023-09-13 Refactor
2023-09-13 Input handling
2023-09-13 Updated settings state to use input handler
2023-09-13 NVM working properly
2023-09-14 Readme thinking about NVM
2023-09-14 Working on EEPROM reset function
2023-09-14 Added custom panic handler
2023-09-14 Added functionality to reset the EEPROM to 0xff
2023-09-14 Was working but rp2040 is bricked
2023-09-14 Fixed, testing caused corrupted NVM
2023-09-14 Executable size optimization
2023-09-19 Start of the farm state
2023-09-19 Restructuring
2023-09-19 Restructured states
2023-09-19 All farm sprites on screen
2023-09-19 Removed vscode issue
2023-09-20 Harvestable indicator
2023-09-20 Farm menuing
2023-09-20 Soil is tillable
2023-09-20 main.rs cleanup
2023-09-20 Starting on rng
2023-09-21 Rng profiling
2023-09-21 rng proof of concept
2023-09-21 Hiding problems from codium
2023-09-21 Minor helper cleanup
2023-09-21 Codium builds for helpers
2023-09-21 Some farm actions are implemented
2023-09-21 Infinity symbol
2023-09-25 Seed bag proof of concept
2023-11-03 Seed inventory persists in nvm
2023-11-13 Fixed data reset issue
2023-11-15 Generalizing seed inv
2024-02-22 Redid menu
2024-02-23 Removed farming and update states
2024-02-23 Enabled 1hz clock
2024-02-24 Pomo time setting
2024-02-24 Connected input to pomo settings
2024-02-24 Disabled 1hz strobe
2024-02-24 Persistant pomo settings
2024-02-27 First pass at color cleanup
2024-02-27 Finished color cleanup
2024-02-27 Makefile, new icons, working on setting components
2024-02-28 Fixed up some temporary patches for the settings
2024-02-28 Reset functionality restored
2024-02-28 Pomo time restored
2024-02-28 Settings are all functional
2024-03-02 Refactored settings
2024-03-02 Ugly first pass at timer - BUG: stop advances phase
2024-03-02 Several fixes
2024-03-02 Better state messages - BUG: pressing stop during pomo #1 goes to short break #1
2024-03-02 Fixed issue with stopping and cleaned up messages
2024-03-02 Moved nvm pages back to normal, adjusted readme
2024-03-02 Removed unused sprites
2024-03-02 Removed unused code
2024-03-03 Major pomo refactor
2024-03-03 Pomo chimes
2024-03-03 A little bit of progress on feeding
2024-03-07 Refactored scenes
2024-03-07 Testing vibration motor
2024-03-07 Timer ending popup
2024-03-07 Added motor to readme
2024-03-08 Todo list
2024-03-08 Top bar added
2024-03-09 Simple inventory
2024-03-09 Inventory nvm
2024-03-09 Reduced inventory abstraction due to bugs
2024-03-09 Better selfdocumentation
2024-03-09 Updated TODO
2024-03-12 Bonuses applied
2024-03-13 Placeholder pomo animation
2024-03-13 Refactored sprite factory
2024-03-13 Dynamic length menu
2024-03-13 Braindump
2024-03-13 Information display improvements
2024-03-14 Updated storage spec
2024-03-15 Alert icon, 2nd core deep sleeping
2024-03-15 Rearranged settings
2024-03-15 Fixed data mapping in readme
2024-03-17 Added audio player
2024-03-18 Rearranged workspace
2024-03-18 Reorganized helpers
2024-03-18 Starting work on track editor
2024-03-19 Improving track editor tui
2024-03-19 Fixed warnings
2024-03-19 Slimmed down track editor and swapped backend
2024-03-19 Track editor minor refactor
2024-03-19 Track editor playback cleanup
2024-03-19 Track editor affected by speed mult
2024-03-19 Cleaning up track editor state management
2024-03-20 Better use of track model
2024-03-20 Track editor read for playback
2024-03-20 Track player
2024-03-20 Sunsetting track editor in favor of player
2024-03-20 Make fix
2024-03-20 Various cleanups
2024-03-20 peat beat conversion works on pico
2024-03-20 Cleaning up process
2024-03-20 Submodule added
2024-03-20 Big restructuring and make improvements
2024-03-20 Removed commented out code
2024-03-20 Added autoplay feature to player
2024-03-21 Updated dependencies
2024-03-21 Updated sprite filenames
2024-03-21 Converted ferris cry to peat
2024-03-21 Reset audio between scene transitions
2024-03-21 Updated pomo scene to new audio system
2024-03-21 TODO updated
2024-03-21 Deadline setting added
2024-03-21 Major improvement to PEAT format
2024-03-22 Prepping for pet nvm
2024-03-22 Pet NVM is constructed
2024-03-22 Readme fix
2024-03-22 Very small cleanups.
2024-03-25 Fixed top bar clock
2024-03-27 Idle state
2024-03-27 Various small changes
2024-03-27 Added todo for stats scene
2024-03-28 Rearranging and removed setting globals
2024-03-28 Reorganized game directories
2024-03-29 Starting on stat scene
2024-04-01 Removed unnecessary make target
2024-04-02 Working on stat scene
2024-05-02 Fps experiments
2024-05-08 Working on datetime
2024-05-09 Time improvements, wip hunger tracking
2024-05-09 Updated repo to comply with warnings from rustc 1.80.0-nightly
2024-08-16 DateTime cleanup
2024-08-16 Fixed excess inventory bug
2024-08-17 Date debugging in stat page
2024-08-17 Working on dt intervals
2024-08-17 dt interval cleanup
2024-08-17 More datetime improvements
2024-08-17 Added Meridian selector, no effect yet
2024-08-17 Selectable AM/PM
2024-08-17 Vibration setting
2024-08-17 Todo update and top bar timer fix
2024-08-17 Missing the deadline inflicts damage
2024-08-17 Placeholder for the setup scene
2024-08-25 Date adjustment setting added
2024-08-25 Beautifying intro scene
2024-08-25 Planning intro scene
2024-09-11 Split wiring between rp2040 boards
2024-09-25 Setting up nix development environment
2024-09-26 Fixing flake
2024-09-26 Flake fix
2025-02-27 Todo and lock updated
2025-03-01 Mostly docs
2025-03-18 Freecad mockup
2025-03-20 Working on kicad schematics
2025-12-09 Fixes for bad flake
2025-12-10 Fixed pwm issue with newer rust
2026-01-13 Reordered pins and various other small changes
2026-01-13 Fixed dependency issue in peat track player
2026-01-13 cve upgrade
2026-01-13 Rust edition specified
2026-01-21 Removed fcbak files, added a few battery sizes to model
2026-01-21 Added 1ah battery
2026-01-21 Weird import issue
2026-01-22 Added tone player on core1 to show core1 can affect the audio engine
2026-01-23 Improved compiler flags, hid warnings that do not apply, and improved build feedback to include ROM utilization
2026-01-29 Enabled wake from interrupt on key3 and the 1hz clock
2026-01-30 Updating schematics
2026-01-31 More schematic work
2026-01-31 Updated gitignore
2026-02-03 Working on a PCB layout, but didn't plan the LCD well enough
2026-02-04 Added vsense pin and debug output in NYI scene
2026-02-05 Redesigning pcb
2026-02-05 Removed remaining kicad backup files
2026-02-05 Working on mcu layout
2026-02-09 Considering making custom RTC module first with pcb fab
2026-02-12 Separated rtc+nvm module for test fabrication
2026-02-13 Added 32-sample averaging to battery reading
2026-02-13 USB module with new mosfet for battery drain prevention
2026-02-18 Moved pcb fab outputs
2026-02-18 Updated fab files for rtc_nvm module
2026-02-19 Updated to 128x160 LCD & custom buttons but the buttons seem buggy
2026-02-20 Various kicad edits
2026-02-20 Several changes but the 1.8 inch screen works well now
2026-02-24 Hiding warnings
2026-02-24 Removing redundant depedencies
2026-02-24 Restored wfi and interrupts on idle state
2026-02-25 Documented dependencies
2026-02-25 Reorganized
2026-02-25 Organized cpu operations
2026-03-03 Updated to ~31FPS with notes on findings
2026-03-03 Accidental early commit
2026-03-03 Adjusted parts & traces on usb kicad
2026-03-04 Working on todo list
2026-03-04 Reduced magic number usage
2026-03-04 Set floods back to dark blue
2026-03-04 Added nvm addr probe
2026-03-05 Error handling and todo cleanup
2026-03-06 Design ideas
2026-03-06 Updating idea docs
2026-03-06 Removed Erroneous Lines
2026-03-06 Added mosfet enable pin, removed alt pin 1, updated var name
2026-03-07 Docs and small makefile update
2026-03-09 More documentation
2026-03-09 Documented most major modules
2026-03-10 Added pulldown resistor, made vsense enable always on
2026-03-13 Swapped the p-channel mosfet for a pnp transistor
